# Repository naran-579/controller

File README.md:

# controller
literally just a game controller in the xbox layout designed for the galaxy a55 5g, but will work for most other smartphones and computers

## how to make

1. Acquire parts from BOM.CSV
2. solder said parts together
3. hot glue the phone case onto the board
4. put a phone in the phone case
5. plug the phone into the board via usb c
6. play your games

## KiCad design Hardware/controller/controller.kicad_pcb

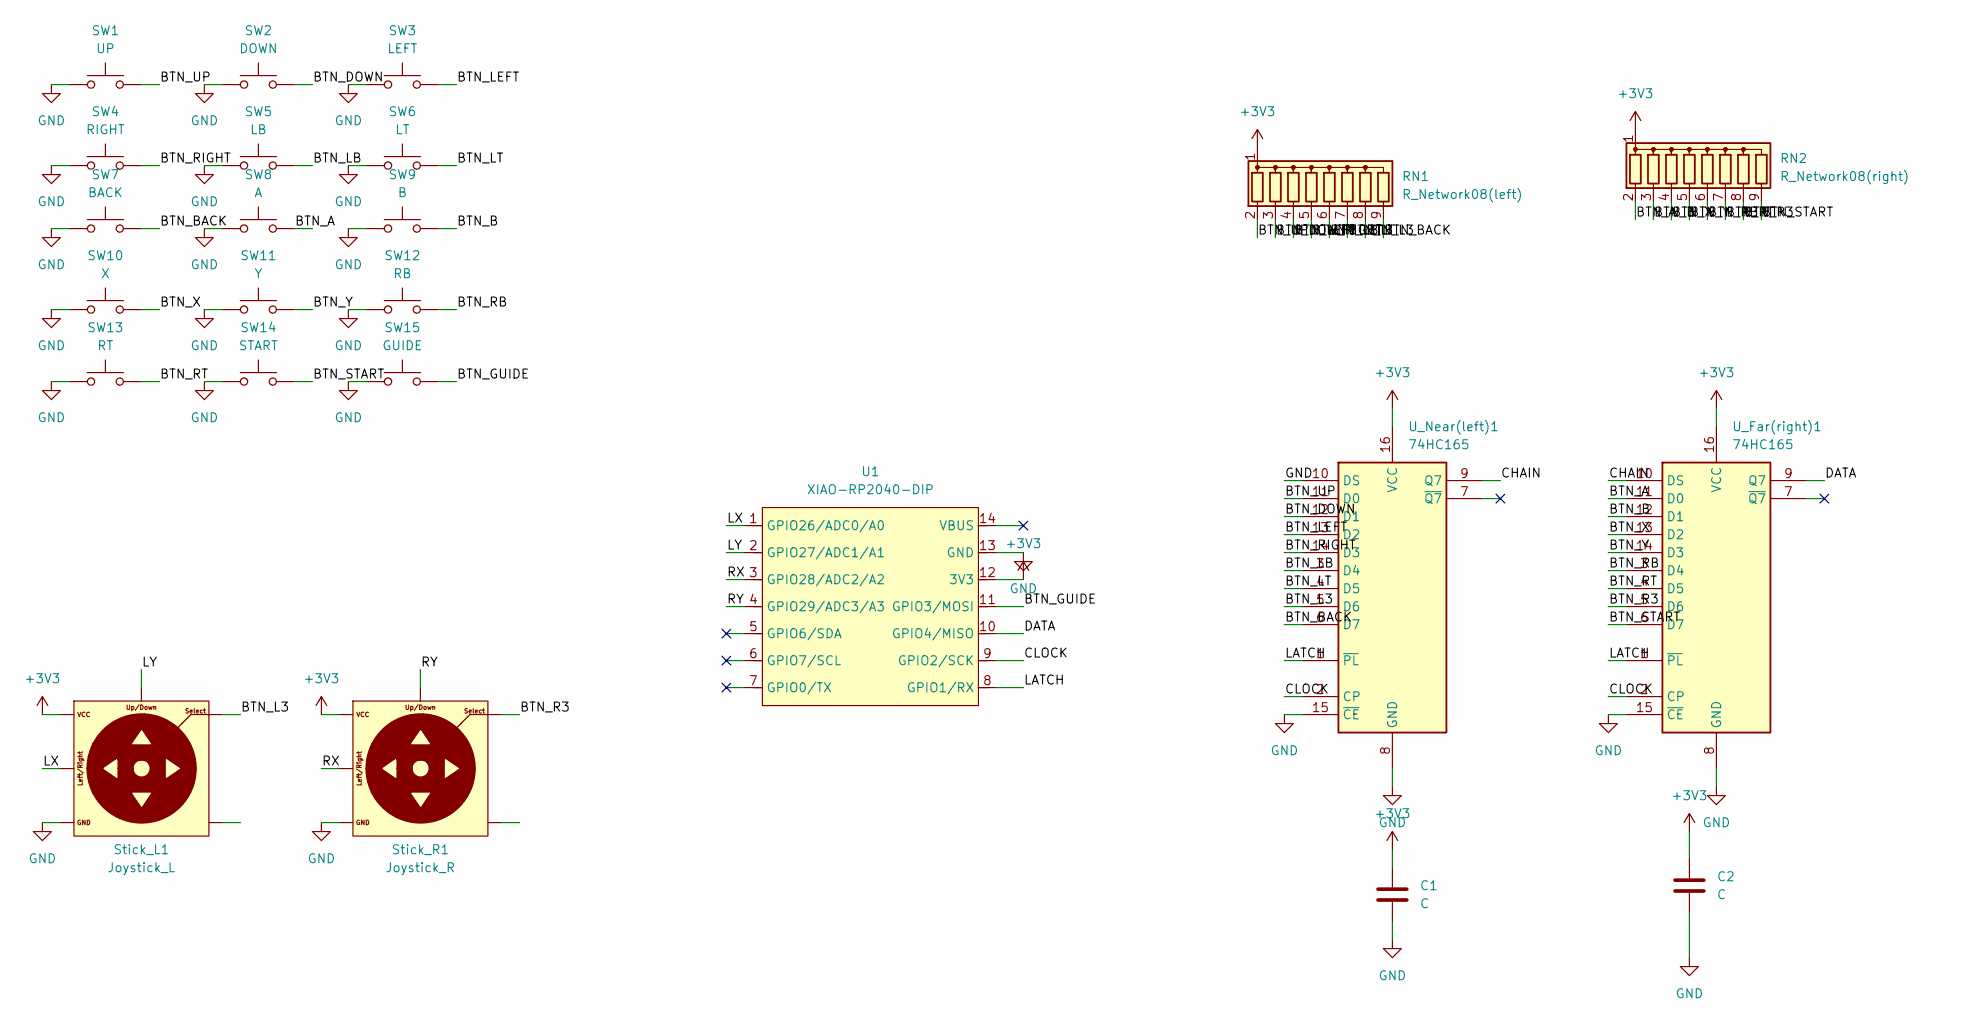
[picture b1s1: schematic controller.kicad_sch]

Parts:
C1, C2: C; C_Disc_D3.0mm_W1.6mm_P2.50mm
RN1: R_Network08(left); R_Array_SIP9
RN2: R_Network08(right); R_Array_SIP9
SW1: UP; Kailh Choc Low-Profile Switches
SW2: DOWN; Kailh Choc Low-Profile Switches
SW3: LEFT; Kailh Choc Low-Profile Switches
SW4: RIGHT; Kailh Choc Low-Profile Switches
SW5: LB; Kailh Choc Low-Profile Switches
SW6: LT; Kailh Choc Low-Profile Switches
SW7: BACK; Kailh Choc Low-Profile Switches
SW8: A; Kailh Choc Low-Profile Switches
SW9: B; Kailh Choc Low-Profile Switches
SW10: X; Kailh Choc Low-Profile Switches
SW11: Y; Kailh Choc Low-Profile Switches
SW12: RB; Kailh Choc Low-Profile Switches
SW13: RT; Kailh Choc Low-Profile Switches
SW14: START; Kailh Choc Low-Profile Switches
SW15: GUIDE; Kailh Choc Low-Profile Switches
Stick_L1: Joystick_L; Joystick_PTH
Stick_R1: Joystick_R; Joystick_PTH
U1: XIAO-RP2040-DIP
U_Far(right)1: 74HC165; DIP-16_W7.62mm
U_Near(left)1: 74HC165; DIP-16_W7.62mm

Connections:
+3V3: C1.1, C2.1, RN1.1 (common), RN2.1 (common), Stick_L1.VCC, Stick_R1.VCC, U1.12 (3V3), U_Far(right)1.16 (VCC), U_Near(left)1.16 (VCC)
/BTN_A: RN2.2 (R1), SW8.2, U_Far(right)1.11 (D0)
/BTN_B: RN2.3 (R2), SW9.2, U_Far(right)1.12 (D1)
/BTN_BACK: RN1.9 (R8), SW7.2, U_Near(left)1.6 (D7)
/BTN_DOWN: RN1.3 (R2), SW2.2, U_Near(left)1.12 (D1)
/BTN_GUIDE: SW15.2, U1.11 (GPIO3/MOSI)
/BTN_L3: RN1.8 (R7), Stick_L1.Select, U_Near(left)1.5 (D6)
/BTN_LB: RN1.6 (R5), SW5.2, U_Near(left)1.3 (D4)
/BTN_LEFT: RN1.4 (R3), SW3.2, U_Near(left)1.13 (D2)
/BTN_LT: RN1.7 (R6), SW6.2, U_Near(left)1.4 (D5)
/BTN_R3: RN2.8 (R7), Stick_R1.Select, U_Far(right)1.5 (D6)
/BTN_RB: RN2.6 (R5), SW12.2, U_Far(right)1.3 (D4)
/BTN_RIGHT: RN1.5 (R4), SW4.2, U_Near(left)1.14 (D3)
/BTN_RT: RN2.7 (R6), SW13.2, U_Far(right)1.4 (D5)
/BTN_START: RN2.9 (R8), SW14.2, U_Far(right)1.6 (D7)
/BTN_UP: RN1.2 (R1), SW1.2, U_Near(left)1.11 (D0)
/BTN_X: RN2.4 (R3), SW10.2, U_Far(right)1.13 (D2)
/BTN_Y: RN2.5 (R4), SW11.2, U_Far(right)1.14 (D3)
/CHAIN: U_Far(right)1.10 (DS), U_Near(left)1.9 (Q7)
/CLOCK: U1.9 (GPIO2/SCK), U_Far(right)1.2 (CP), U_Near(left)1.2 (CP)
/DATA: U1.10 (GPIO4/MISO), U_Far(right)1.9 (Q7)
/LATCH: U1.8 (GPIO1/RX), U_Far(right)1.1 (~PL), U_Near(left)1.1 (~PL)
/LX: Stick_L1.Horizontal, U1.1 (GPIO26/ADC0/A0)
/LY: Stick_L1.Vertical, U1.2 (GPIO27/ADC1/A1)
/RX: Stick_R1.Horizontal, U1.3 (GPIO28/ADC2/A2)
/RY: Stick_R1.Vertical, U1.4 (GPIO29/ADC3/A3)
GND: C1.2, C2.2, SW1.1, SW2.1, SW3.1, SW4.1, SW5.1, SW6.1, SW7.1, SW8.1, SW9.1, SW10.1, SW11.1, SW12.1, SW13.1, SW14.1, SW15.1, Stick_L1.GND, Stick_R1.GND, U1.13 (GND), U_Far(right)1.8 (GND), U_Far(right)1.15 (~CE), U_Near(left)1.8 (GND), U_Near(left)1.10 (DS), U_Near(left)1.15 (~CE)

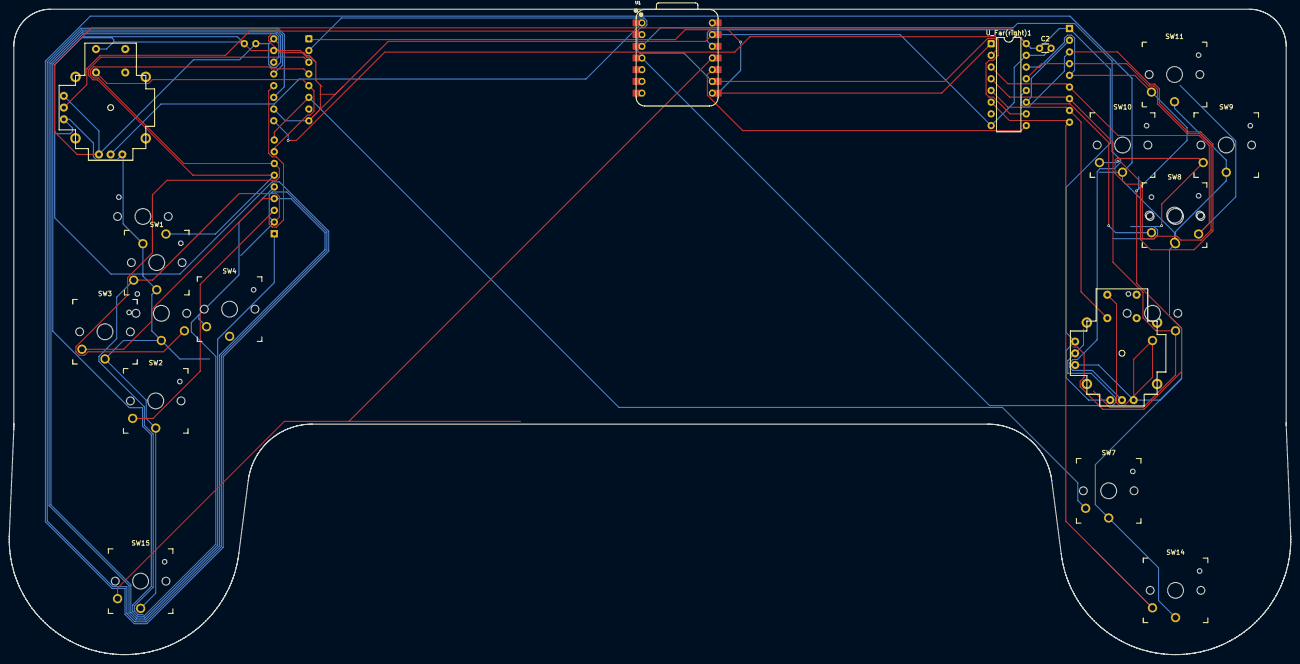
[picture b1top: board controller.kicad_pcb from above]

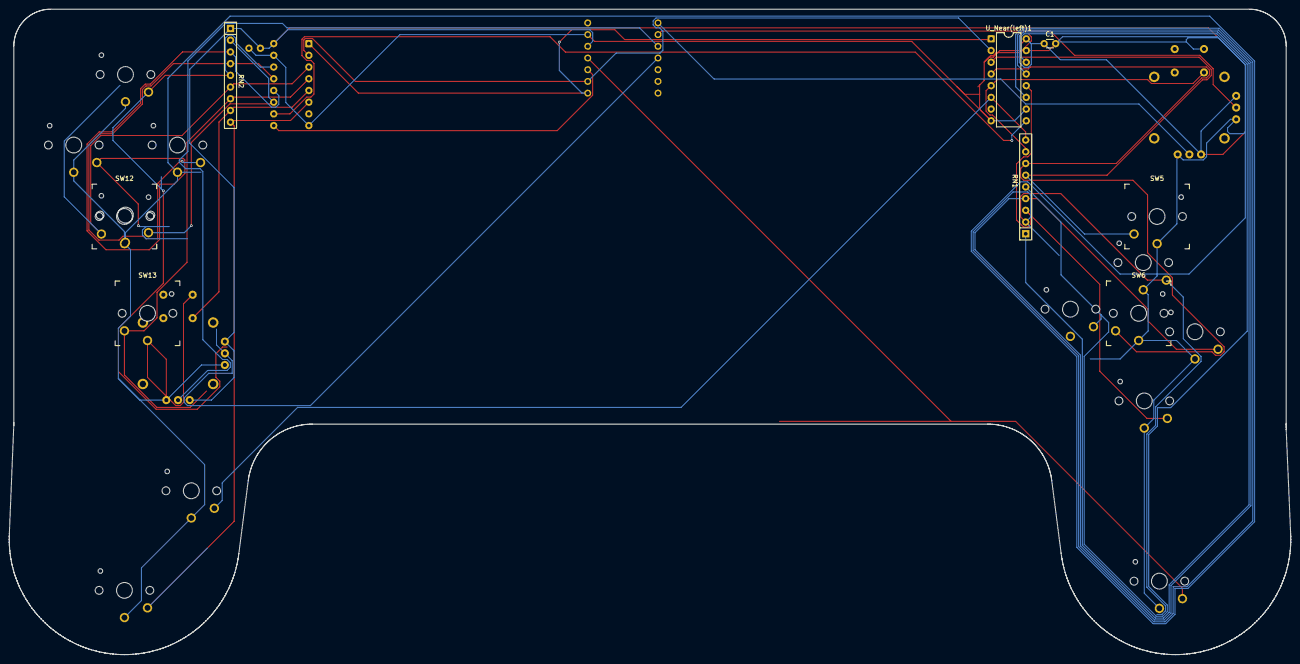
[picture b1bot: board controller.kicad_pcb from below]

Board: 2 copper layers, 278.0 x 140.0 mm, 24 parts (8 on the bottom side), 27 nets.
